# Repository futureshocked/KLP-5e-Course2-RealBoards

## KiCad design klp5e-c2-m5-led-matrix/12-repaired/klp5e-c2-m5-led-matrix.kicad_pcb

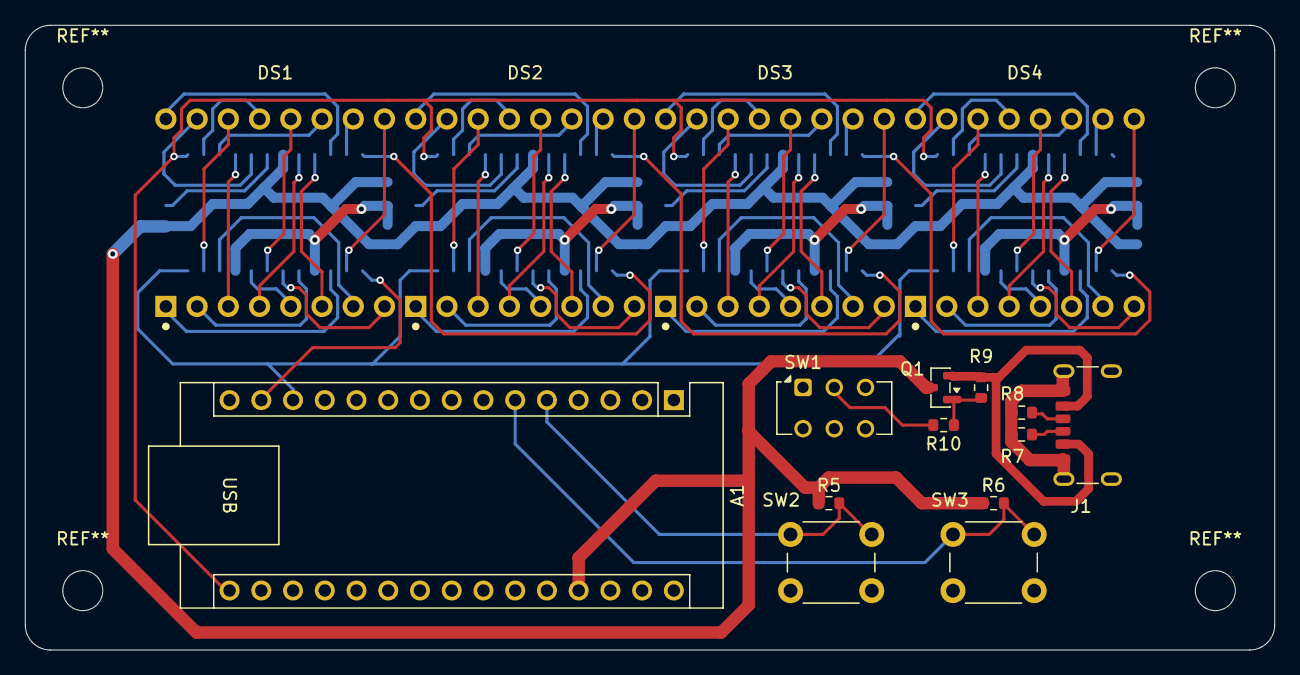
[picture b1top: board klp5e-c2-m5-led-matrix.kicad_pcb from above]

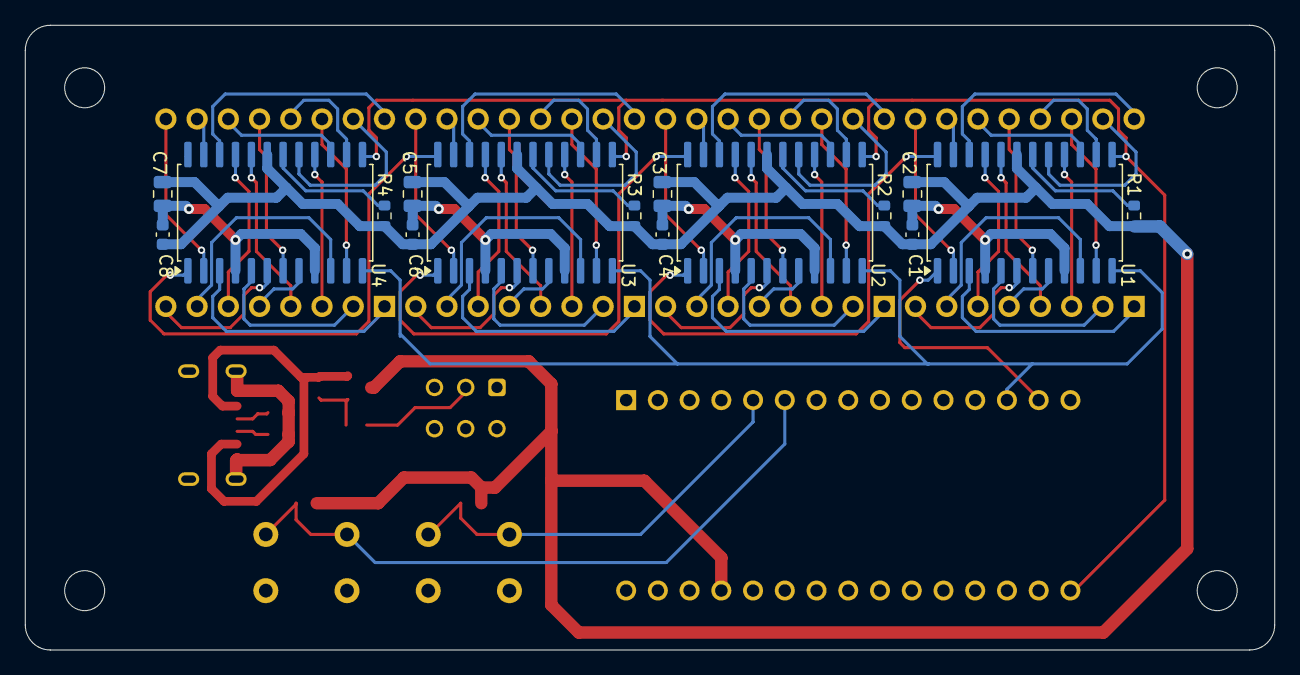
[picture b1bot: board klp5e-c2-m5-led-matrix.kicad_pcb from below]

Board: 2 copper layers, 100.0 x 50.0 mm, 32 parts (16 on the bottom side), 83 nets.

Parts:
A1: Arduino_Nano_v3.x; Arduino_Nano
C1, C4, C6, C8: 100n; C_0603_1608Metric
C2, C3, C5, C7: 10u; C_0805_2012Metric
DS1, DS2, DS3, DS4: LED_Matrix_TA08-81GWA; LED_Matrix_TA08-81_20mm_8x8
J1: USB_C_Receptacle_PowerOnly_6P; USB_C_Receptacle_GCT_USB4125-xx-x-0190_6P_TopMnt_Horizontal
Q1: AO3401A; SOT-23
R1, R2, R3, R4: 12k; R_0603_1608Metric
R5, R6, R10: 10k; R_0603_1608Metric
R7, R8: 5.1k; R_0603_1608Metric
R9: 100k; R_0603_1608Metric
SW1: SW_SPDT; SW_CK_JS202011AQN_DPDT_Angled
SW2, SW3: SW_Push; SW_PUSH_6mm
U1, U2, U3, U4: MAX7219; SOIC-24W_7.5x15.4mm_P1.27mm

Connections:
+5V: A1.27 (+5V), C1.1, C2.1, C3.1, C4.1, C5.1, C6.1, C7.1, C8.1, Q1.3 (D), R1.1, R2.1, R3.1, R4.1, R5.1, R6.1, U1.19 (V+), U2.19 (V+), U3.19 (V+), U4.19 (V+)
/CLK: A1.16 (D13), U1.13 (CLK), U2.13 (CLK), U3.13 (CLK), U4.13 (CLK)
/DIN1: A1.14 (D11), U1.1 (DIN)
/LINK1: U1.24 (DOUT), U2.1 (DIN)
/LINK2: U2.24 (DOUT), U3.1 (DIN)
/LINK3: U3.24 (DOUT), U4.1 (DIN)
/LOAD: A1.13 (D10), U1.12 (LOAD), U2.12 (LOAD), U3.12 (LOAD), U4.12 (LOAD)
/MODE: A1.5 (D2), R5.2, SW2.1
/SELECT: A1.6 (D3), R6.2, SW3.1
GND: A1.4 (GND), A1.29 (GND), C1.2, C2.2, C3.2, C4.2, C5.2, C6.2, C7.2, C8.2, J1.A12 (GND), J1.B12 (GND), J1.SH (SHIELD), R7.2, R8.2, SW1.1 (A), SW2.2, SW3.2, U1.4 (GND), U1.9 (GND), U2.4 (GND), U2.9 (GND), U3.4 (GND), U3.9 (GND), U4.4 (GND), U4.9 (GND)
unnamed: DS1.13 (COL1), U1.14 (SEG_A)
unnamed: DS1.3 (COL2), U1.16 (SEG_B)
unnamed: DS1.4 (COL3), U1.20 (SEG_C)
unnamed: DS1.10 (COL4), U1.23 (SEG_D)
unnamed: DS1.6 (COL5), U1.21 (SEG_E)
unnamed: DS1.11 (COL6), U1.15 (SEG_F)
unnamed: DS1.15 (COL7), U1.17 (SEG_G)
unnamed: DS1.16 (COL8), U1.22 (SEG_DP)
unnamed: DS1.9 (ROW1), U1.2 (DIG_0)
unnamed: DS1.14 (ROW2), U1.11 (DIG_1)
unnamed: DS1.8 (ROW3), U1.6 (DIG_2)
unnamed: DS1.12 (ROW4), U1.7 (DIG_3)
unnamed: DS1.1 (ROW5), U1.3 (DIG_4)
unnamed: DS1.7 (ROW6), U1.10 (DIG_5)
unnamed: DS1.2 (ROW7), U1.5 (DIG_6)
unnamed: DS1.5 (ROW8), U1.8 (DIG_7)
unnamed: DS2.13 (COL1), U2.14 (SEG_A)
unnamed: DS2.3 (COL2), U2.16 (SEG_B)
unnamed: DS2.4 (COL3), U2.20 (SEG_C)
unnamed: DS2.10 (COL4), U2.23 (SEG_D)
unnamed: DS2.6 (COL5), U2.21 (SEG_E)
unnamed: DS2.11 (COL6), U2.15 (SEG_F)
unnamed: DS2.15 (COL7), U2.17 (SEG_G)
unnamed: DS2.16 (COL8), U2.22 (SEG_DP)
unnamed: DS2.9 (ROW1), U2.2 (DIG_0)
unnamed: DS2.14 (ROW2), U2.11 (DIG_1)
unnamed: DS2.8 (ROW3), U2.6 (DIG_2)
unnamed: DS2.12 (ROW4), U2.7 (DIG_3)
unnamed: DS2.1 (ROW5), U2.3 (DIG_4)
unnamed: DS2.7 (ROW6), U2.10 (DIG_5)
unnamed: DS2.2 (ROW7), U2.5 (DIG_6)
unnamed: DS2.5 (ROW8), U2.8 (DIG_7)
unnamed: DS3.13 (COL1), U3.14 (SEG_A)
unnamed: DS3.3 (COL2), U3.16 (SEG_B)
unnamed: DS3.4 (COL3), U3.20 (SEG_C)
unnamed: DS3.10 (COL4), U3.23 (SEG_D)
unnamed: DS3.6 (COL5), U3.21 (SEG_E)
unnamed: DS3.11 (COL6), U3.15 (SEG_F)
unnamed: DS3.15 (COL7), U3.17 (SEG_G)
unnamed: DS3.16 (COL8), U3.22 (SEG_DP)
unnamed: DS3.9 (ROW1), U3.2 (DIG_0)
unnamed: DS3.14 (ROW2), U3.11 (DIG_1)
unnamed: DS3.8 (ROW3), U3.6 (DIG_2)
unnamed: DS3.12 (ROW4), U3.7 (DIG_3)
unnamed: DS3.1 (ROW5), U3.3 (DIG_4)
unnamed: DS3.7 (ROW6), U3.10 (DIG_5)
unnamed: DS3.2 (ROW7), U3.5 (DIG_6)
unnamed: DS3.5 (ROW8), U3.8 (DIG_7)
unnamed: DS4.13 (COL1), U4.14 (SEG_A)
unnamed: DS4.3 (COL2), U4.16 (SEG_B)
unnamed: DS4.4 (COL3), U4.20 (SEG_C)
unnamed: DS4.10 (COL4), U4.23 (SEG_D)
unnamed: DS4.6 (COL5), U4.21 (SEG_E)
unnamed: DS4.11 (COL6), U4.15 (SEG_F)
unnamed: DS4.15 (COL7), U4.17 (SEG_G)
unnamed: DS4.16 (COL8), U4.22 (SEG_DP)
unnamed: DS4.9 (ROW1), U4.2 (DIG_0)
unnamed: DS4.14 (ROW2), U4.11 (DIG_1)
unnamed: DS4.8 (ROW3), U4.6 (DIG_2)
unnamed: DS4.12 (ROW4), U4.7 (DIG_3)
unnamed: DS4.1 (ROW5), U4.3 (DIG_4)
unnamed: DS4.7 (ROW6), U4.10 (DIG_5)
unnamed: DS4.2 (ROW7), U4.5 (DIG_6)
unnamed: DS4.5 (ROW8), U4.8 (DIG_7)
unnamed: J1.A5 (CC1), R7.1
unnamed: J1.B5 (CC2), R8.1
unnamed: Q1.1 (G), R9.2, R10.1
unnamed: R10.2, SW1.2 (B)
unnamed: R1.2, U1.18 (ISET)
unnamed: R2.2, U2.18 (ISET)
unnamed: R3.2, U3.18 (ISET)
unnamed: R4.2, U4.18 (ISET)
VBUS: J1.A9 (VBUS), J1.B9 (VBUS), Q1.2 (S), R9.1

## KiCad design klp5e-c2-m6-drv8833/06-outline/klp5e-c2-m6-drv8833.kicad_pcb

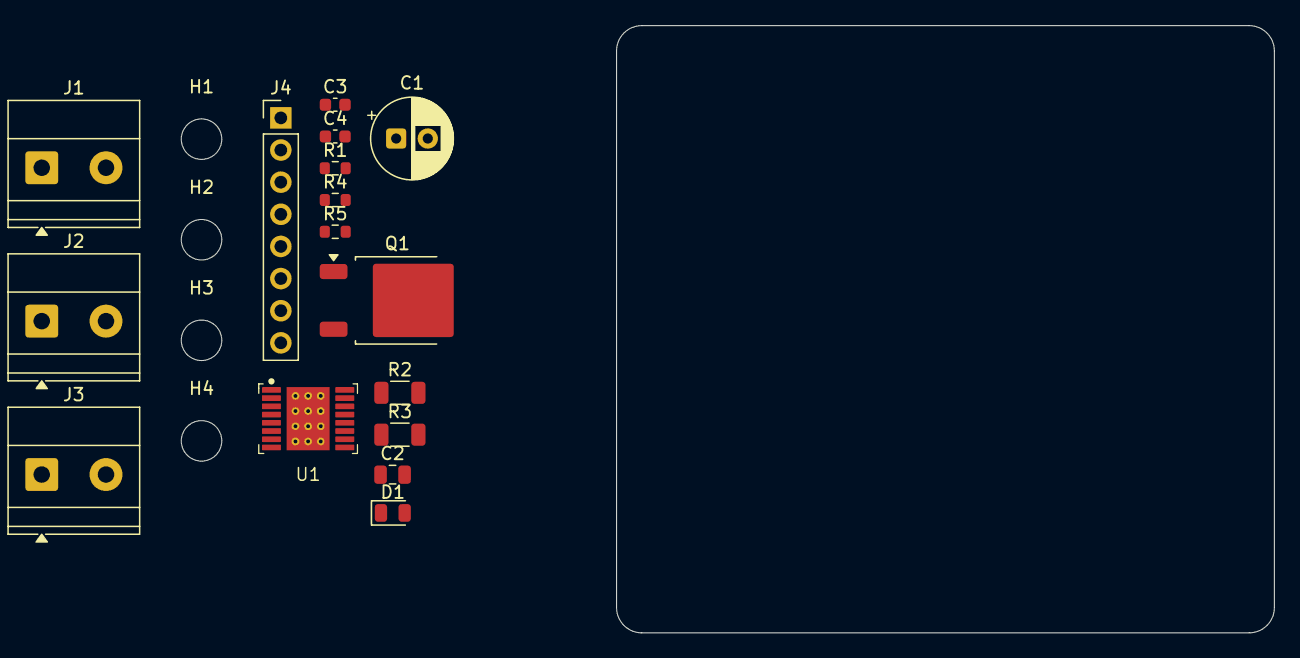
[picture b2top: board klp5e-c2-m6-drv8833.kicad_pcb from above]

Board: 2 copper layers, 52.0 x 48.0 mm, 20 parts (0 on the bottom side), 20 nets, no tracks yet.

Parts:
C1: 100uF 25V; CP_Radial_D6.3mm_P2.50mm
C2: 10uF 25V; C_0805_2012Metric
C3: 0.01uF 16V; C_0603_1608Metric
C4: 2.2uF 16V; C_0603_1608Metric
D1: LED; LED_0805_2012Metric
H1, H2, H3, H4: MountingHole; MountingHole_3.2mm_M3
J1, J2, J3: Conn_01x02; TerminalBlock_Phoenix_MKDS-1,5-2-5.08_1x02_P5.08mm_Horizont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
J4: Conn_01x08; PinHeader_1x08_P2.54mm_Vertical
Q1: SUD45P03-09; TO-252-2
R1: 10k; R_0603_1608Metric
R2, R3: 0R2; R_1206_3216Metric
R4: 100k; R_0603_1608Metric
R5: 1k; R_0603_1608Metric
U1: DRV8833; HTSSOP-16-1EP_DRV8833_PD

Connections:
/AIN1: J4.5, U1.16 (AIN1)
/AIN2: J4.6, U1.15 (AIN2)
/AISEN: R2.1, U1.3 (AISEN)
/AOUT1: J2.1, U1.2 (AOUT1)
/AOUT2: J2.2, U1.4 (AOUT2)
/BIN1: J4.7, U1.9 (BIN1)
/BIN2: J4.8, U1.10 (BIN2)
/BISEN: R3.1, U1.6 (BISEN)
/BOUT1: J3.1, U1.7 (BOUT1)
/BOUT2: J3.2, U1.5 (BOUT2)
/GATE: Q1.1 (G), R4.1
/VCP: C3.2, U1.11 (VCP)
/VINT: C4.2, U1.14 (VINT)
/VLOGIC: J4.1, R1.2
/VM: C1.1, C2.2, C3.1, Q1.3 (S), R5.1, U1.12 (VM)
/VM_IN: J1.1, Q1.2 (D)
/nFAULT: J4.4, R1.1, U1.8 (nFAULT)
/nSLEEP: J4.3, U1.1 (nSLEEP)
GND: C1.2, C2.1, C4.1, D1.1 (K), J1.2, J4.2, R2.2, R3.2, R4.2, U1.13 (GND), U1.17 (PAD)
unnamed: D1.2 (A), R5.2
